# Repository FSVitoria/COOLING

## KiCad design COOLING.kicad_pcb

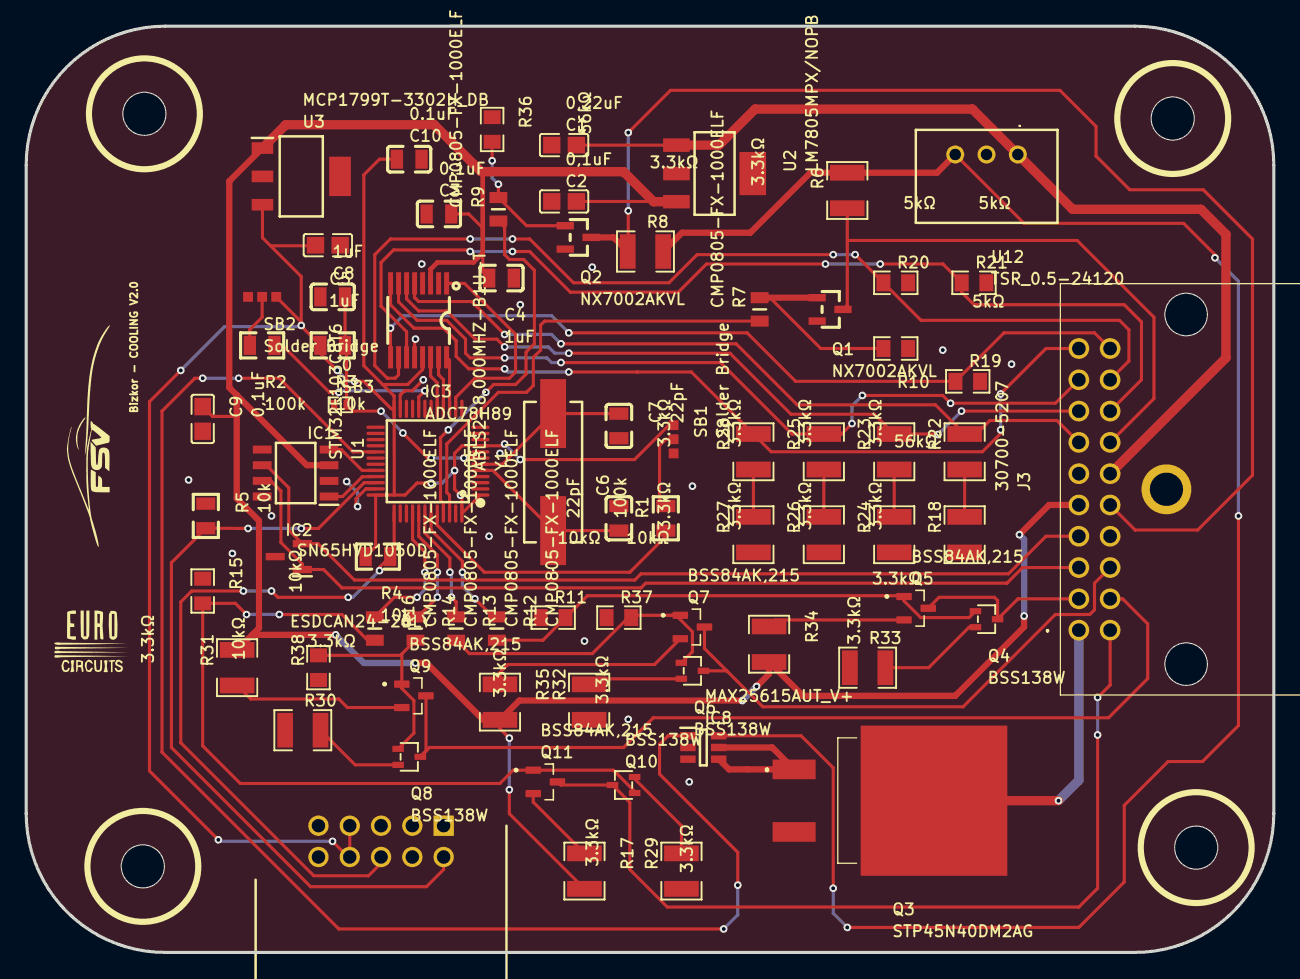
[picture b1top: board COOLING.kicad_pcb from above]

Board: 2 copper layers, 101.3 x 75.2 mm, 77 parts (0 on the bottom side), 62 nets.

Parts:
C1: 0,22uF; C0805
C2, C9: 0,1uF; C0805
C3, C10: 0.1uF; C0805
C4, C5, C8: 1uF; C0805
C6, C7: 22pF; C0805
Hole_gge23215: Hole_gge23215
Hole_gge24187: Hole_gge24187
Hole_gge24235: Hole_gge24235
Hole_gge24295: Hole_gge24295
IC1: SN65HVD1050D; SOIC127P600X175-8N
IC2: ESDCAN24-2BLY; SOT105P255X150-3N
IC3: ADC78H89; TSSOP-16_L5.0-W4.4-P0.65-LS6.4-BL
IC8: MAX25615AUT_V+; SOT95P280X145-6N
J2: 61201021721; SHDRRA10W64P254X254_2X5_2036X8
J3: 30700-5207; 307005207
Q1, Q2: NX7002AKVL; TO-236AB_L2.9-W1.3-P0.95-LS2.3-BR
Q3: STP45N40DM2AG; STP45N40DM2A ARREGLO
Q4, Q6, Q8, Q10: BSS138W; SOT-323-3_L2.0-W1.3-P1.30-LS2.1-BR
Q5, Q7, Q9, Q11: BSS84AK,215; SOT95P230X110-3N
R1, R2: 100k; R0805
R3, R4, R5: 10k; R0805
R6, R8, R17, R18, R22, R23, R24, R25, R26, R27, R28, R29, R30, R31, R32, R33, R34, R35: 3.3kΩ; R1210
R7, R9, R12, R13, R14, R16: CMP0805-FX-1000ELF; RESC2012X60N
R10: 56kΩ; R0402
R11, R15, R37, R38: 10kΩ; R0805
R19, R20, R21: 5kΩ; R0805
R36: 56kΩ; 0402
SB1, SB2: Solder Bridge; SOLDER BRDIGE
SB3: 0; R0402
U1: STM32F103C8T6; LQFP-48_L7.0-W7.0-P0.50-LS9.0-BL
U2: LM7805MPX/NOPB; SOT-223
U3: MCP1799T-3302H_DB; SOT230P700X180-4N
U12: TSR_0.5-24120; TSR0524120
Y1: ABLS2-8.000MHZ-B1U-T; ABLS

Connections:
3V3: C5.2, C10.1, IC3.13, J2.7, J2.8, R3.2, R4.2, SB1.1, SB2.1, U1.1, U1.9, U1.24, U1.36, U1.48, U3.3
+5V: C2.2, C3.2, C4.2, C9.1, IC1.3, IC3.3, J3.5, R17.2, R31.2, R34.2, R35.2, U2.3, U3.1
+12V: IC8.6, R6.2, R8.2, U12.3
+24V: C1.2, J3.16, U2.1, U12.1
BOOT0: R1.1, U1.44
BOOT1: R2.1, U1.20
BRAKE_LIGHT_GND: J3.1, Q3.2
CAN_H: IC1.7, IC2.1, J3.3
CAN_L: IC1.6, IC2.2, J3.4
CAN_RX: IC1.4, U1.32
CAN_TX: IC1.1, U1.33
GND: C1.1, C2.1, C3.1, C4.1, C5.1, C6.2, C7.2, C8.1, C9.2, C10.2, IC1.2, IC1.8, IC2.3, IC3.4, IC3.12, IC8.2, IC8.3, J2.3, J2.4, J3.6, J3.14, J3.MH1, Q1.2, Q2.2, Q3.3, R5.1, R10.1, R11.1, R15.1, R18.1, R19.2, R20.2, R21.2, R24.1, R26.1, R27.1, R29.1, R30.1, R32.1, R33.1, R36.1, R37.1, R38.1, SB1.3, SB2.3, SB3.1, U1.8, U1.23, U1.35, U1.47, U2.2, U2.4, U3.2, U3.4, U12.2
MCU_BREAK_LIGHT: IC8.1, U1.29
MCU_FAN_1: R12.1, U1.43
MCU_FAN_2: R13.1, U1.42
MCU_FAN_3: R14.1, U1.41
MCU_FAN_4: R16.1, U1.40
MCU_PUMP_1: R7.1, U1.46
MCU_PUMP_2: R9.1, U1.45
MEASURE_1: IC3.5, J3.7, R22.2
MEASURE_2: IC3.6, J3.8, R23.2
MEASURE_3: IC3.7, J3.9, R25.2
MEASURE_4: IC3.8, J3.10, R28.2
MEASURE_5: IC3.9, J3.20, R19.1
MEASURE_6: IC3.10, J3.19, R20.1
MEASURE_7: IC3.11, J3.18, R21.1
PWM1: J3.17, Q1.3, R6.1
PWM2: J3.15, Q2.3, R8.1
PWM3: J3.2, Q4.3, Q5.3
PWM4: J3.13, Q6.3, Q7.3
PWM5: J3.12, Q8.3, Q9.3
PWM6: J3.11, Q10.3, Q11.3
Q1_1: Q1.1, R7.2, R10.2
Q3_1: IC8.4, IC8.5, Q3.1
Q4_2: Q4.2, R33.2
Q5_1: Q4.1, Q5.1, R11.2, R12.2
Q5_2: Q5.2, R34.1
Q6_2: Q6.2, R32.2
Q7_1: Q6.1, Q7.1, R13.2, R37.2
Q7_2: Q7.2, R35.1
Q8_1: Q8.1, Q9.1, R14.2, R38.2
Q8_2: Q8.2, R30.2
Q9_2: Q9.2, R31.1
Q10_1: Q10.1, Q11.1, R15.2, R16.2
Q10_2: Q10.2, R29.2
Q11_2: Q11.2, R17.1
R9_2: Q2.1, R9.2, R36.2
R18_2: R18.2, R22.1
R23_1: R23.1, R24.2
R25_1: R25.1, R26.2
R27_2: R27.2, R28.1
RST: C8.2, R3.1, SB3.2, U1.7
SB1_2: R1.2, SB1.2
SB2_2: R2.2, SB2.2
SPI_CS1: IC3.1, U1.14
SPI_MISO: IC3.15, U1.16
SPI_MOSI: IC3.14, U1.17
SPI_SCK: IC3.16, U1.15
SWCLK: J2.6, R4.1, U1.37
SWDIO: J2.2, R5.2, U1.34
Y1_1: C6.1, U1.5, Y1.1
Y1_2: C7.1, U1.6, Y1.2
